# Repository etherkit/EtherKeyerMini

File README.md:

# EtherKeyer Mini

A simple keyer that does the basic functions that you need.

## Requirements

In order to program the message memories, change parameters other than the keyer speed, and update the firmware, you'll need a serial terminal that can connect to the 5 V TTL UART on EtherKeyer Mini via the 3.5 mm TRRS paddle jack. The Etherkit UART Adapter board has a USB-C connection for your PC and the requisite 3.5 mm TRRS jack, so that all that you need to connect to EtherKeyer Mini is a 3.5 mm TRRS cable.

A CR2032 lithium coin cell is required for powering EtherKeyer Mini.

## Functions

### Speed Potentiometer

The knob control on the right side of the front of EtherKeyer Mini controls the keyer speed, from a minimum of 5 WPM to a maximum of 40 WPM. This control can be adjusted at any time and responds immediately.

### Pushbuttons

#### Short Press

Cancel any message playback by pressing any button or paddle.

- 1 - Play Message Memory 1
- 2 - Play Message Memory 2
- 3 - Play Message Memory 3

#### Long Press

- 1 - Tune Mode (press any key to exit, otherwise exits after 30 seconds)
- 2 - Toggle Internal Sidetone
- 3 - Enter/Exit UART Mode

### UART Mode

The format for interacting with EtherKeyer Mini via the UART is very simple. In order to place EtherKeyer Mini into UART mode, press and hold button 3 for at least one second. If your serial terminal is open when you do this, you'll get a greeting from EtherKeyer Mini to let you know it is ready for commands.

Each message memory has a maximum size of 40 characters.

Exit UART mode by pressing and holding button 3 again for at least one second, or issue the ```X:``` command in the serial terminal. UART mode also returns to keyer mode after 60 seconds without a received line, so the keyer can go back to sleep.

#### Serial Terminal Parameters

19200 baud, send New Line only, no flow control.

#### Query

- ```W?``` - Keyer speed
- ```1?``` - Message memory 1
- ```2?``` - Message memory 2
- ```3?``` - Message memory 3

#### Parameter Set

- ```1:<message>``` - Message memory 1
- ```2:<message>``` - Message memory 2
- ```3:<message>``` - Message memory 3
- ```X:``` - Exit UART Mode
- ```R:``` - Reverse Paddle Terminals
- ```N:``` - Normal Paddle Terminals
- ```A:``` - Set Iambic A Mode
- ```B:``` - Set Iambic B Mode
- ```S:``` - Sidetone On
- ```O:``` - Sidetone Off

## Firmware Updates

__Please see the Requirements section above for the hardware necessary for the UART adapter.__

EtherKeyer Mini uses an ATtiny3226 microcontroller with the Optiboot bootloader pre-installed. You can use load new firmware onto EtherKeyer Mini via a UART adapter connected to the paddle jack (the easiest way to do so is using the Etherkit UART Adapter board with a 3.5 mm TRRS cable). You can also use a standard USB-UART adapter connected to jack J3 to program the ATtiny3226 via UPDI protocol.

Programming via the paddle jack is accomplished using the Arduino IDE using the [megaTinyCore](https://github.com/SpenceKonde/megaTinyCore) board support package. Use [this link](https://github.com/SpenceKonde/megaTinyCore/blob/master/Installation.md) for instructions on how to add this board support package to your Arduino IDE. Once you have added the board support package, connect your UART adapter to your PC. In Arduino IDE, select the "ATtiny3226/1626/826/426 w/Optiboot" as your board and port corresponding to your programming UART adapter. Make sure to set all of the specific board settings in the Tools menu of Arduino IDE to those shown below:

Once you have all of these settings correct, you can load the EtherKeyerMini.ino sketch into the Arduino IDE and then use the Sketch > Upload menu command or use the upload button on the toolbar.

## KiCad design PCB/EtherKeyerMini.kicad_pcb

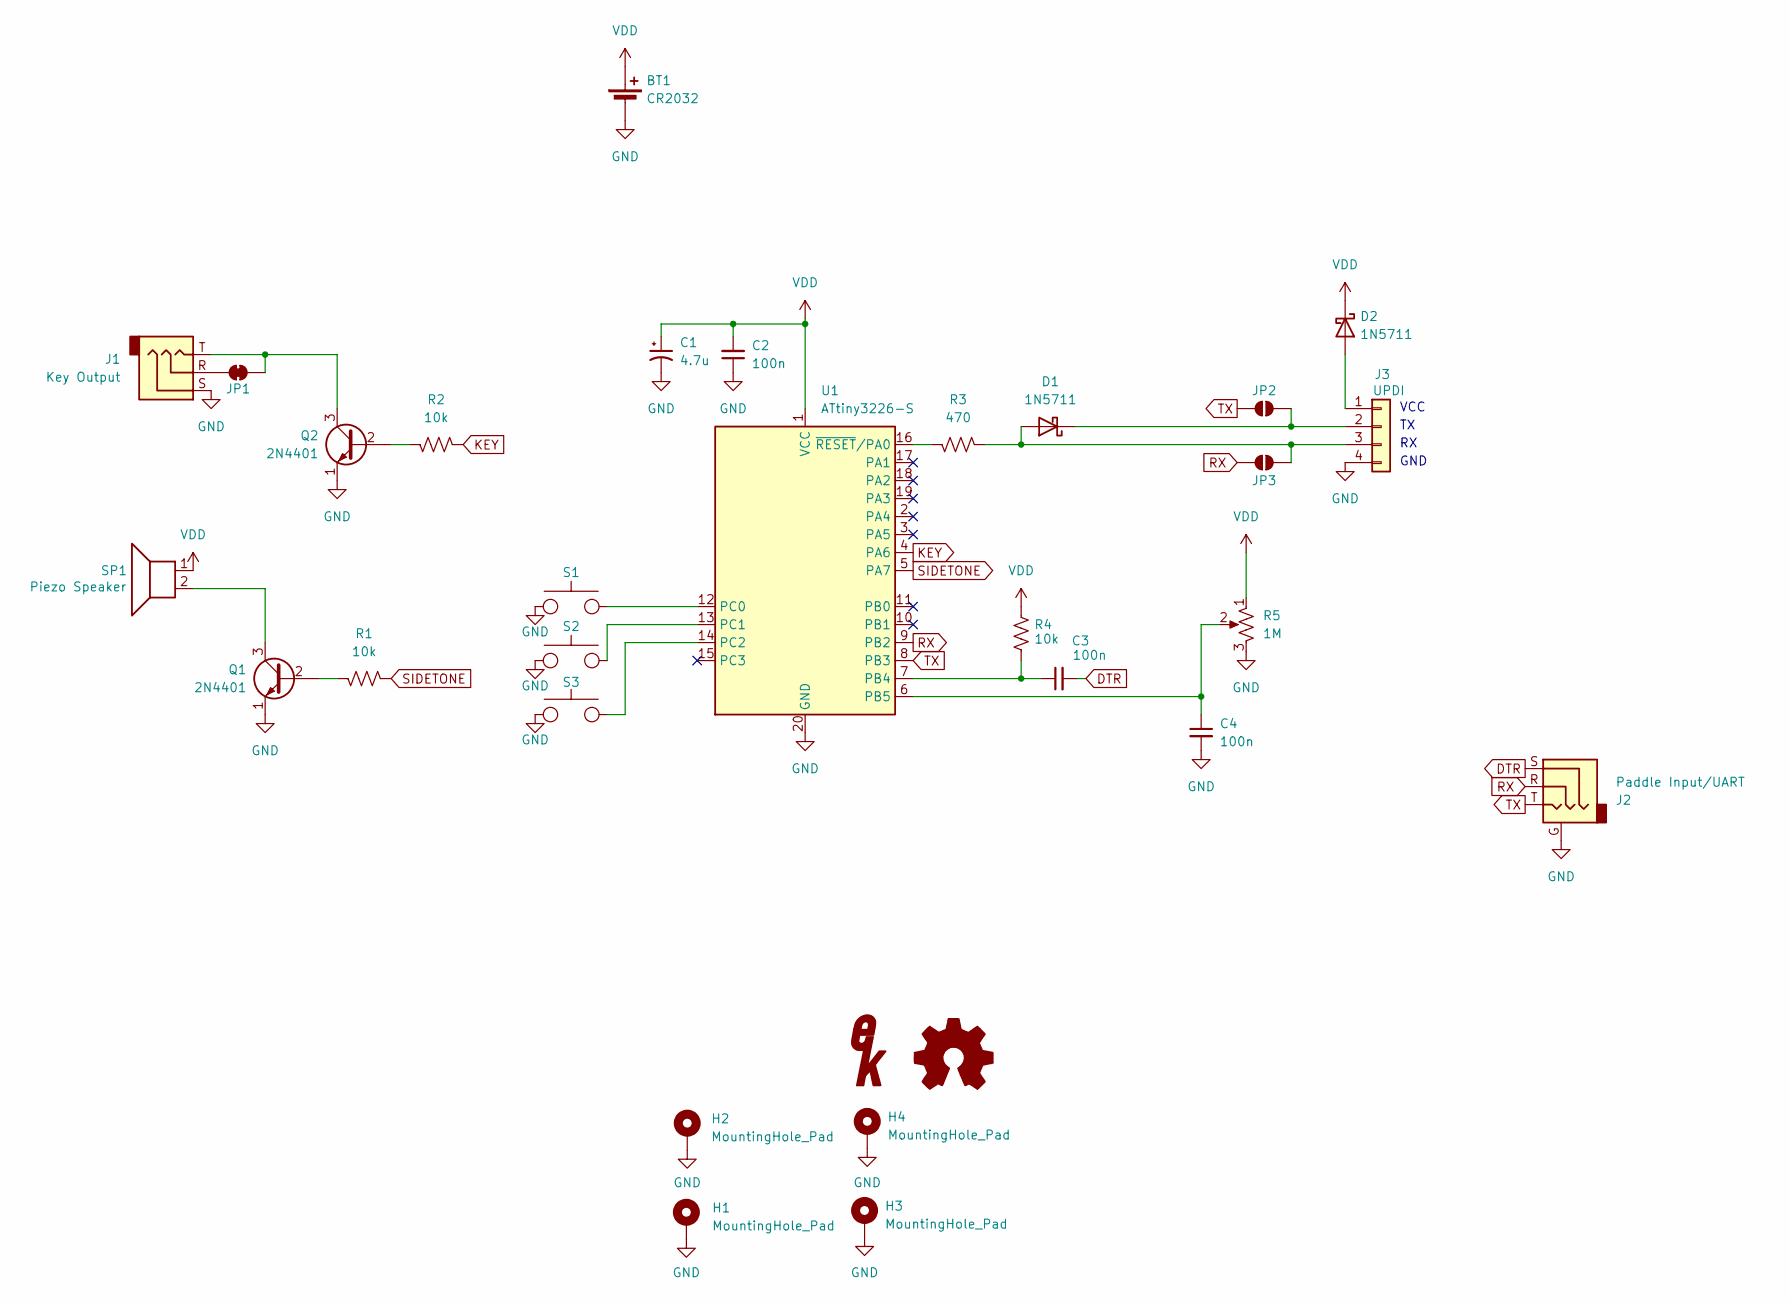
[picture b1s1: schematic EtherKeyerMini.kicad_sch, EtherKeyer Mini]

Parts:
BT1: CR2032; Linx_BAT-HLD-001
C1: 4.7u; CP_Radial_D6.3mm_P2.50mm
C2, C3, C4: 100n; C_Rect_L7.0mm_W2.5mm_P5.00mm
D1, D2: 1N5711; D_DO-35_SOD27_P7.62mm_Horizontal
G1: LOGO; EtherkitLogoSmall
H1, H2, H3, H4: MountingHole_Pad; MountingHole_3.2mm_M3_Pad_Via
J1: Key Output; Kycon_STX-3120-3B
J2: Paddle Input/UART; SameSky_SJ-43514
J3: UPDI; PinSocket_1x04_P2.54mm_Vertical
JP1: SolderJumper_2_Bridged; SolderJumper-2_P1.3mm_Bridged_RoundedPad1.0x1.5mm
JP2, JP3: SolderJumper_2_Bridged; SolderJumper-2_P1.3mm_Open_RoundedPad1.0x1.5mm
Q1, Q2: 2N4401; TO-92_Inline
R1, R2, R4: 10k; R_Axial_DIN0207_L6.3mm_D2.5mm_P2.54mm_Vertical
R3: 470; R_Axial_DIN0207_L6.3mm_D2.5mm_P2.54mm_Vertical
R5: 1M; Bournes_PTV09A
S1, S2, S3: PUSHBUTTON_TACTILE; C&K_PTS645VH832LFS
SP1: Piezo Speaker; PUI_AT-1224-TWT-12V-2-R
SYM1: Logo_Open_Hardware_Small; OSHWLogo4mm
U1: ATtiny3226-S; SOIC-20W_7.5x12.8mm_P1.27mm

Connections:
DTR: C3.2, J2.S
GND: BT1.2 (-), C1.2, C2.1, C4.2, H1.1, H2.1, H3.1, H4.1, J1.S, J2.G, J3.4, Q1.1 (E), Q2.1 (E), R5.3, S1.1, S2.1, S3.1, U1.20 (GND)
KEY: R2.2, U1.4 (PA6)
unnamed: D1.2 (A), J3.3, JP3.2 (B), R3.2
unnamed: D1.1 (K), J3.2, JP2.2 (B)
unnamed: D2.2 (A), J3.1
unnamed: J1.R, JP1.1 (A)
unnamed: J1.T, JP1.2 (B), Q2.3 (C)
unnamed: Q1.2 (B), R1.1
unnamed: Q1.3 (C), SP1.2
unnamed: Q2.2 (B), R2.1
unnamed: C3.1, R4.2, U1.7 (PB4)
unnamed: C4.1, R5.2, U1.6 (PB5)
unnamed: S1.2, U1.12 (PC0)
unnamed: S2.2, U1.13 (PC1)
unnamed: S3.2, U1.14 (PC2)
unnamed: R3.1, U1.16 (~RESET/PA0)
RX: J2.R, JP3.1 (A), U1.9 (PB2)
SIDETONE: R1.2, U1.5 (PA7)
TX: J2.T, JP2.1 (A), U1.8 (PB3)
VDD: BT1.1 (+), C1.1, C2.2, D2.1 (K), R4.1, R5.1, SP1.1, U1.1 (VCC)

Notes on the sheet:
GND
VCC

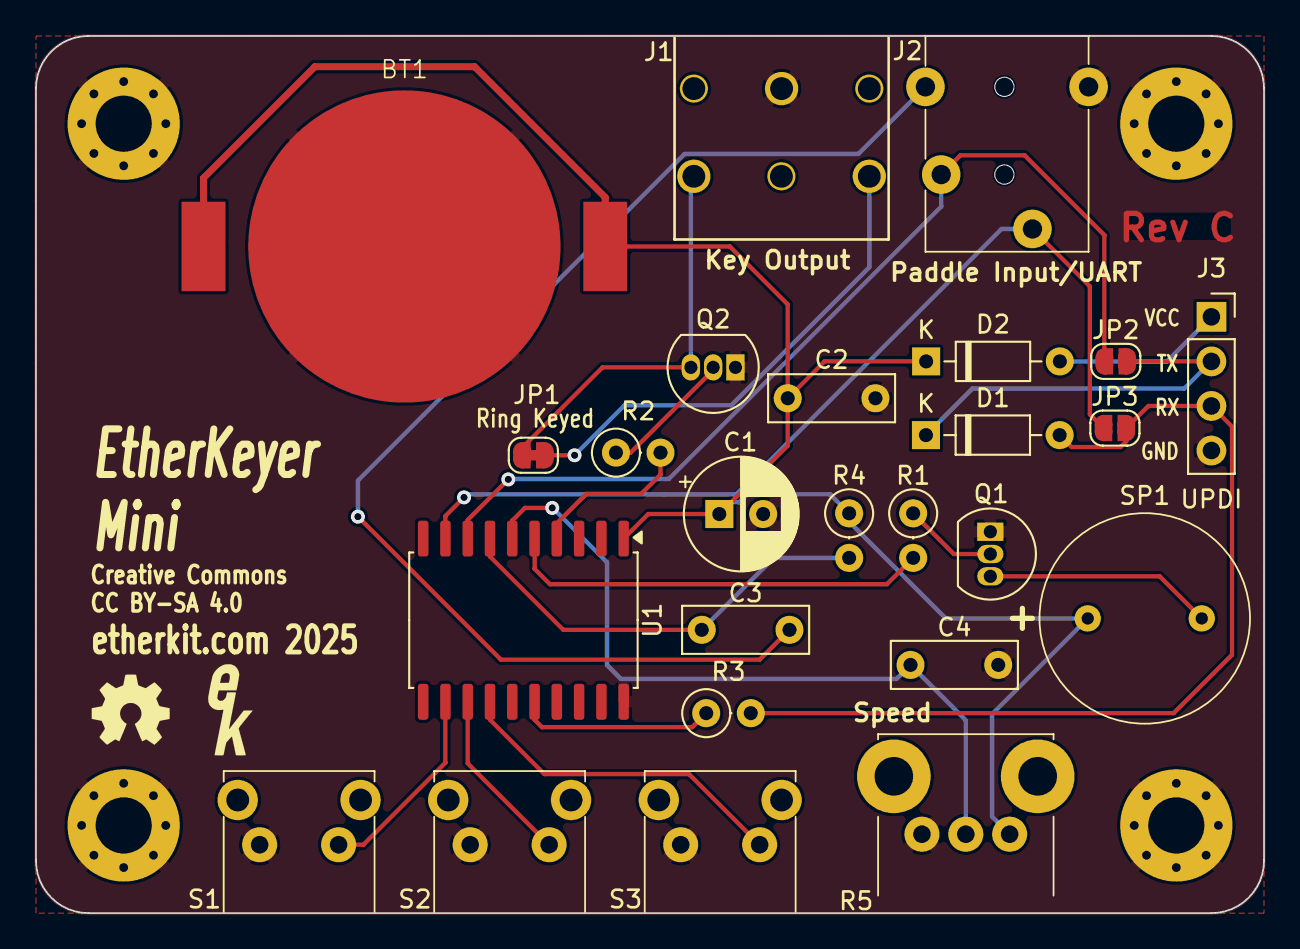
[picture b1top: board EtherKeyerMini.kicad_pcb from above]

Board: 2 copper layers, 70.0 x 50.0 mm, 31 parts (0 on the bottom side), 21 nets.

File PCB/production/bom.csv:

Designator,Footprint,Quantity,Value,LCSC Part #
BT1,Linx_BAT-HLD-001,1,CR2032,
C1,CP_Radial_D6.3mm_P2.50mm,1,4.7u,
"C2, C3, C4",C_Rect_L7.0mm_W2.5mm_P5.00mm,3,100n,
"D1, D2",D_DO-35_SOD27_P7.62mm_Horizontal,2,1N5711,
J1,Kycon_STX-3120-3B,1,Key Output,
J2,SameSky_SJ-43514,1,Paddle Input/UART,
J3,PinSocket_1x04_P2.54mm_Vertical,1,UPDI,
"Q1, Q2",TO-92_Inline,2,2N4401,
"R1, R2, R4",R_Axial_DIN0207_L6.3mm_D2.5mm_P2.54mm_Vertical,3,10k,
R3,R_Axial_DIN0207_L6.3mm_D2.5mm_P2.54mm_Vertical,1,470,
R5,Bournes_PTV09A,1,1M,
"S1, S2, S3",C&K_PTS645VH832LFS,3,PUSHBUTTON_TACTILE,
SP1,PUI_AT-1224-TWT-12V-2-R,1,Piezo Speaker,
U1,SOIC-20W_7.5x12.8mm_P1.27mm,1,ATtiny3226-S,

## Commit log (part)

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2024-01-13 Schematic update
2024-01-13 Fix keyer timing in firmware
2024-01-14 Fix WDT settings in firmware
2024-01-28 Add BOM, update bootloader and firmware for ATtiny85V
2024-01-29 Re-enable sleep in firmware
2024-01-29 Update EtherKeyerMiniBOM.txt
    Fix typo in transistor part number
2024-01-30 Update docs, add paddle rev to firmware
2024-01-30 Some firmware size optimization
2024-02-21 Add license terms
2024-02-22 Add tune mode, fix reverse keying
2024-02-23 Implement Iambic A/B
2024-02-23 Fix error in Iambic keying
2024-02-25 Update documentation
2024-07-10 Rev B PCB
2024-07-25 Update image and README
2024-07-25 Freeze firmware for upcoming refactoring
2024-08-14 Reduce code size, add sidetone
2024-08-14 Fix sleep bug on tune
2024-08-15 Update schematic, include built firmware
2024-08-21 Fix keying bug, move keying detection in to loop
2024-09-06 Documentation update for Beta
2024-09-06 More documentation fixes
2024-09-18 Fix dit emitted on startup
2025-04-08 Rev C PCB
2025-04-08 Update PDF schematic
2025-04-19 Final firmware for Rev B PCB
2025-05-12 Firmware update to support PCB Rev C
2025-06-14 Update documentation to support PCB Rev C

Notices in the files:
PCB/EtherKeyerMini.kicad_pcb:
Creative Commons
CC BY-SA 4.0
